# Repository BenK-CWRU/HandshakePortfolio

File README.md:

This repository contains some of the work I have done using simulation software and EDAs such as LTSpice and KiCad.

The FinalSchem_rev7 folder contains the KiCad project files for the amplitude shift keying and frequency shift keying demodulator circuit.

The ASKFSKDemodulatorFinalSchematic.asc file is the LTSpice file to simulate the amplitude shift keying and frequency shift keying demodulator.

DP2OpAmp.asc is an op amp design I made in LTSpice.

LDO is a low dropout linear regulator design I made in LTSpice.

OscillatorFunctionGen.asc is a function generator design I made in LTSpice.

PWMtoOptoDevice.asc is a PWM generator based on an external signal that is coupled to an optoelectronic device to output the same PWM signal. I designed this in LTSpice.

kHzClockGen.asc is an astable oscillator circuit that was made to generate a 1 kHz clock signal, which I designed in LTSpice.

I also have more experience with Autodesk Fusion, but most of the work is closely related to lab work that has yet to be patented.
Without disclosing the whole work, I have designed a circuit that contains a microcontroller which periodically polls an on-board pressure sensor.
It contained wireless power harvesting circuitry, so it could be powered with an inductive link to a source coil.
It was a two-layer board with tight trace routing. I researched the tolerances with our PCB vendor before layout to ensure I could design the smallest board possible.

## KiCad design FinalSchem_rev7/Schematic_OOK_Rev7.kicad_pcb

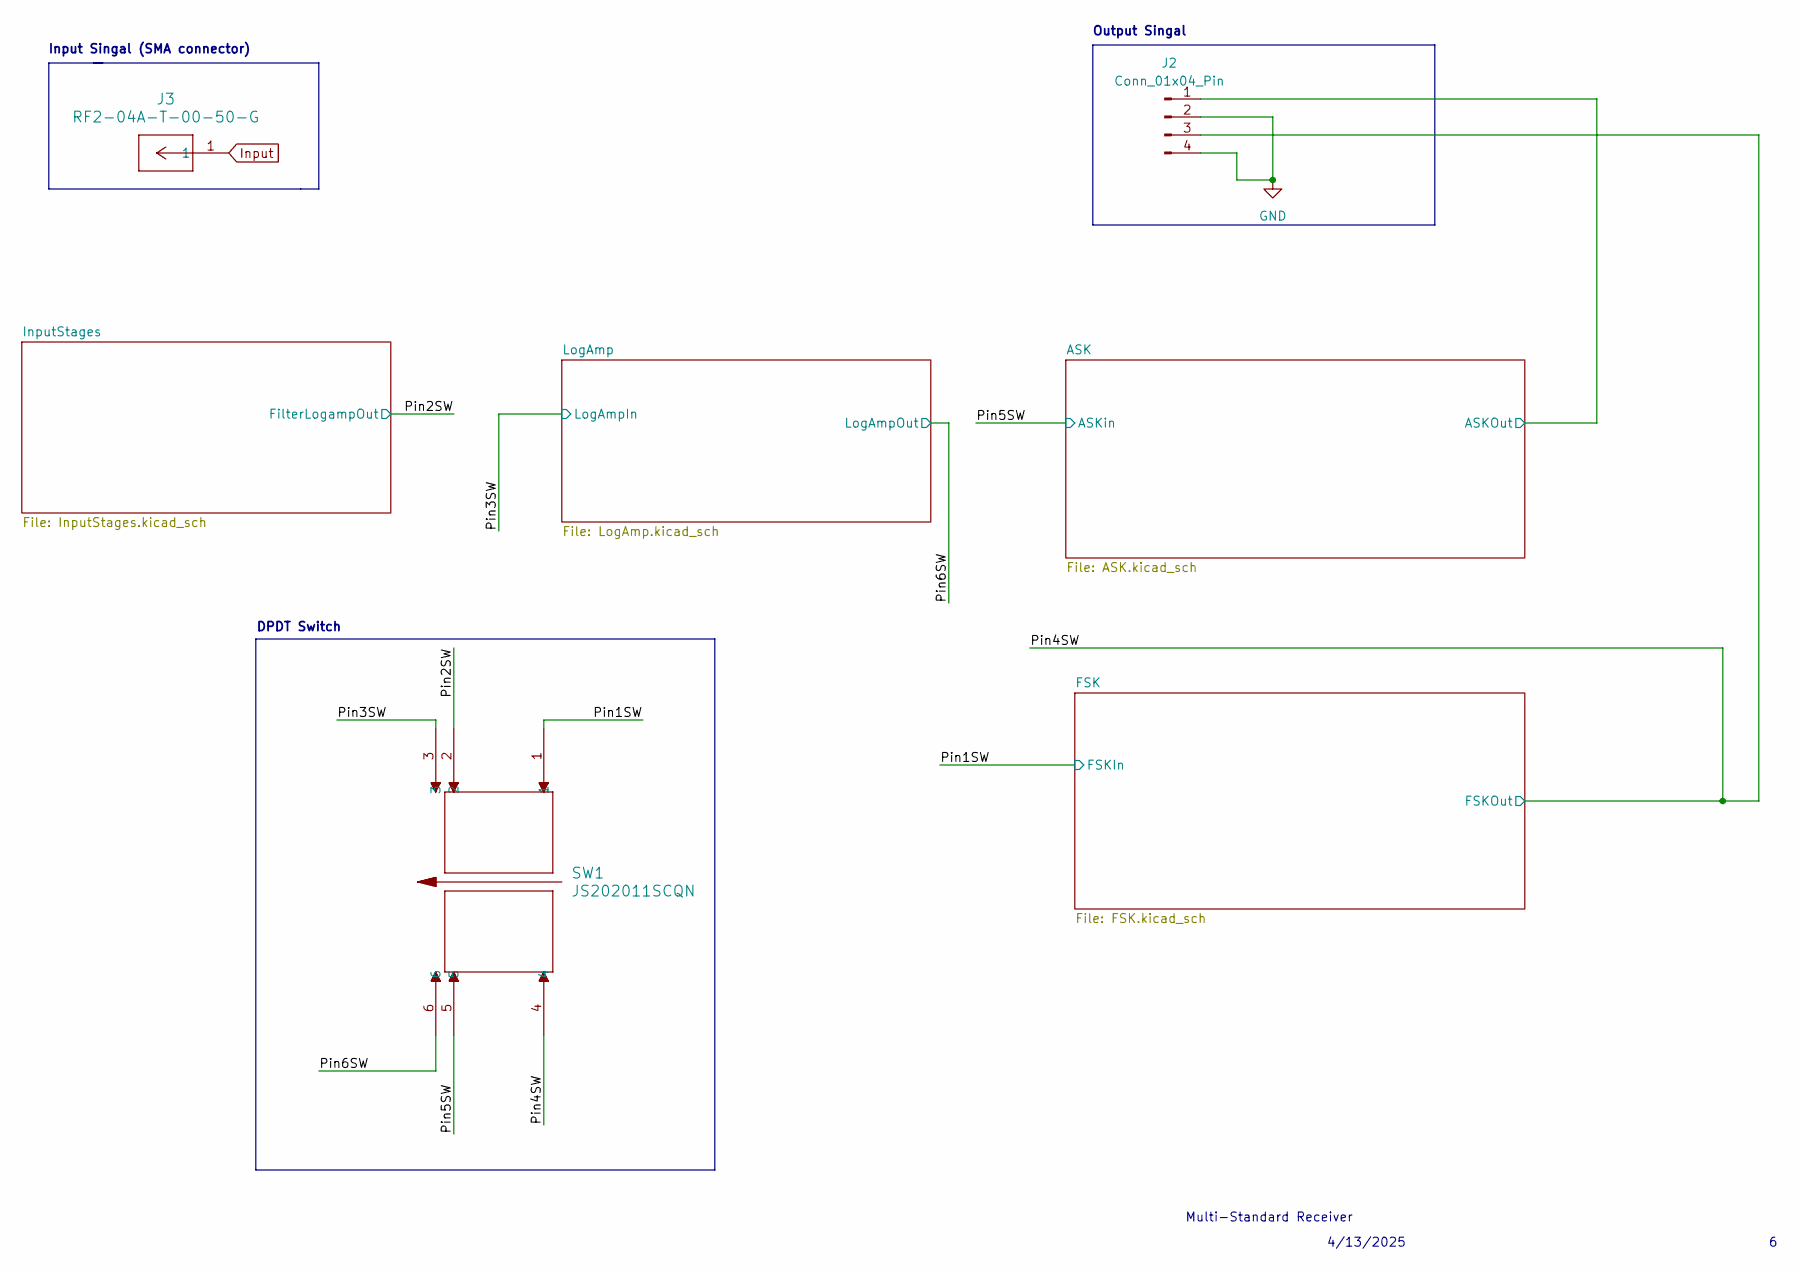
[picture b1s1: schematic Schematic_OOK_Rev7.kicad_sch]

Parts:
J2: Conn_01x04_Pin; PinHeader_1x04_P2.54mm_Vertical
J3: RF2-04A-T-00-50-G; CONN_RF2-04A-T-00-50-G_ADM
SW1: JS202011SCQN

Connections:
/ASK/ASKOut: J2.1; also elsewhere on the board
/Pin1SW: SW1.1; also elsewhere on the board
/Pin2SW: SW1.2; also elsewhere on the board
/Pin3SW: SW1.3; also elsewhere on the board
/Pin4SW: J2.3, SW1.4; also elsewhere on the board
/Pin5SW: SW1.5; also elsewhere on the board
/Pin6SW: SW1.6; also elsewhere on the board
GND: J2.2, J2.4; also elsewhere on the board
Input: J3.1; also elsewhere on the board

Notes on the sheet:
Output Singal
Input Singal (SMA connector)
4/13/2025
Multi-Standard Receiver
DPDT Switch

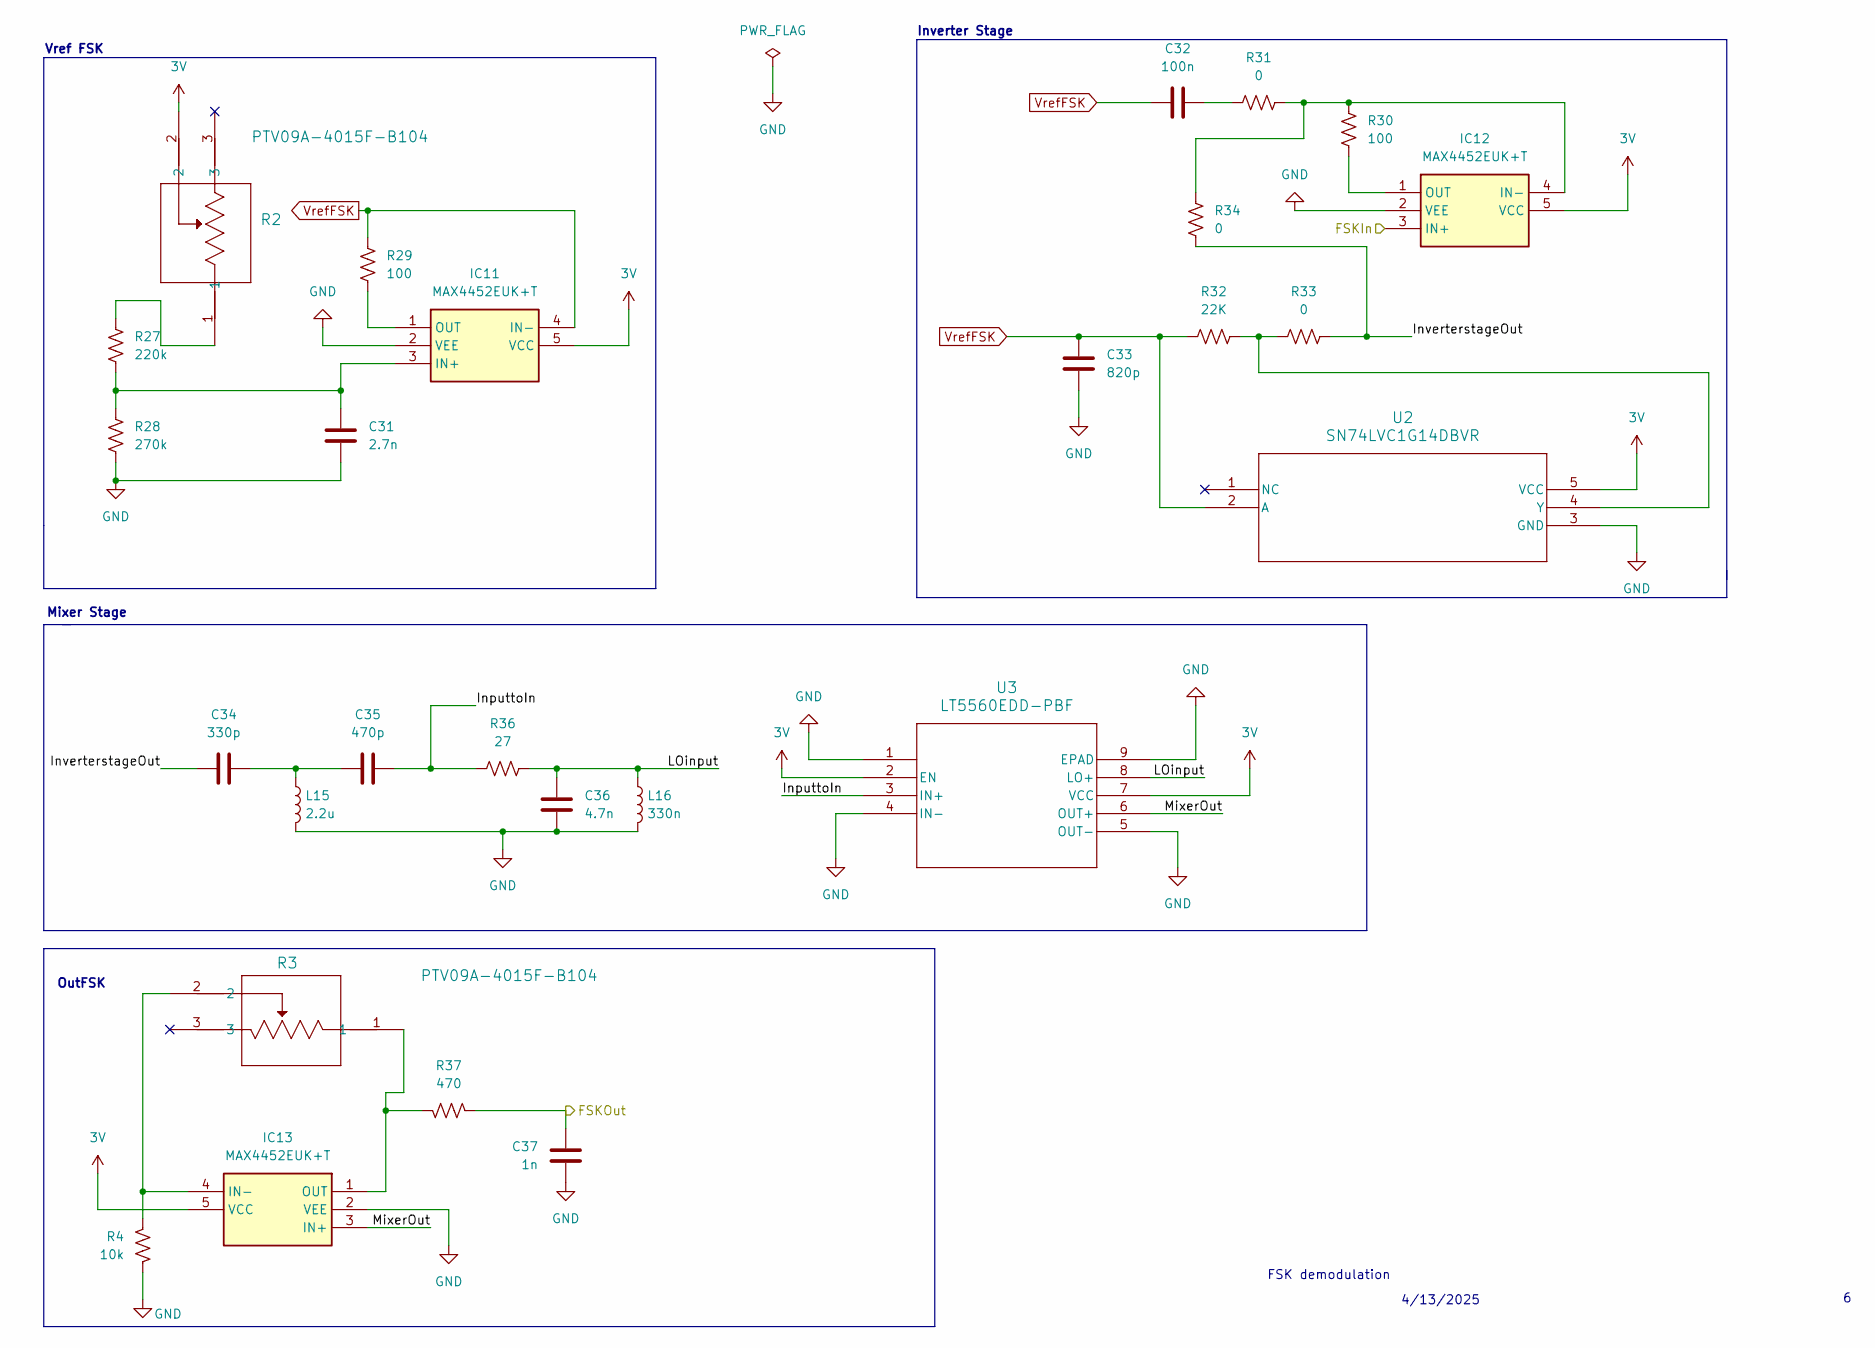
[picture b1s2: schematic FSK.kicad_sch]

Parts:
C31: 2.7n; C_0603_1608Metric
C32: 100n; C_0603_1608Metric
C33: 820p; C_0603_1608Metric
C34: 330p; C_0603_1608Metric
C35: 470p; C_0603_1608Metric
C36: 4.7n; C_0603_1608Metric
C37: 1n; C_0603_1608Metric
IC11, IC12, IC13: MAX4452EUK+T; SOT95P280X145-5N; Mouser Part Number 700-MAX4452EUKT
L15: 2.2u; L_0603_1608Metric
L16: 330n; L_0603_1608Metric
R2, R3: PTV09A-4015F-B104; PTV09A-4015F-B104_BRN
R4: 10k; R_0603_1608Metric
R27: 220k; R_0603_1608Metric
R28: 270k; R_0603_1608Metric
R29, R30: 100; R_0603_1608Metric
R31, R33, R34: 0; R_0603_1608Metric
R32: 22K; R_0603_1608Metric
R36: 27; R_0603_1608Metric
R37: 470; R_0603_1608Metric
U2: SN74LVC1G14DBVR
U3: LT5560EDD-PBF; LT556EDD-PBF

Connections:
3V: IC11.5 (VCC), IC12.5 (VCC), IC13.5 (VCC), R2.2, U2.5 (VCC), U3.2 (EN), U3.7 (VCC); also elsewhere on the board
/FSK/InputtoIn: C35.2, R36.1, U3.3 (IN+)
/FSK/InverterstageOut: C34.1, R33.2, R34.1
/FSK/LOinput: C36.2, L16.1, R36.2, U3.8 (LO+)
/FSK/MixerOut: IC13.3 (IN+), U3.6 (OUT+)
/Pin1SW: IC12.3 (IN+); also elsewhere on the board
/Pin4SW: C37.2, R37.2; also elsewhere on the board
GND: C31.1, C33.1, C36.1, C37.1, IC11.2 (VEE), IC12.2 (VEE), IC13.2 (VEE), L15.2, L16.2, R4.2, R28.2, U2.3 (GND), U3.1, U3.4 (IN-), U3.5 (OUT-), U3.9 (EPAD); also elsewhere on the board
unnamed: C32.1, R31.1
unnamed: C34.2, C35.1, L15.1
unnamed: C31.2, IC11.3 (IN+), R27.2, R28.1
unnamed: IC11.1 (OUT), R29.2
unnamed: IC12.4 (IN-), R30.1, R31.2, R34.2
unnamed: IC12.1 (OUT), R30.2
unnamed: IC13.4 (IN-), R3.2, R4.1
unnamed: IC13.1 (OUT), R3.1, R37.1
unnamed: R2.1, R27.1
unnamed: R32.1, R33.1, U2.4 (Y)
VrefFSK: C32.2, C33.2, IC11.4 (IN-), R29.1, R32.2, U2.2 (A)

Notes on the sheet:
Mixer Stage
Vref FSK
FSK demodulation
4/13/2025
Inverter Stage
OutFSK

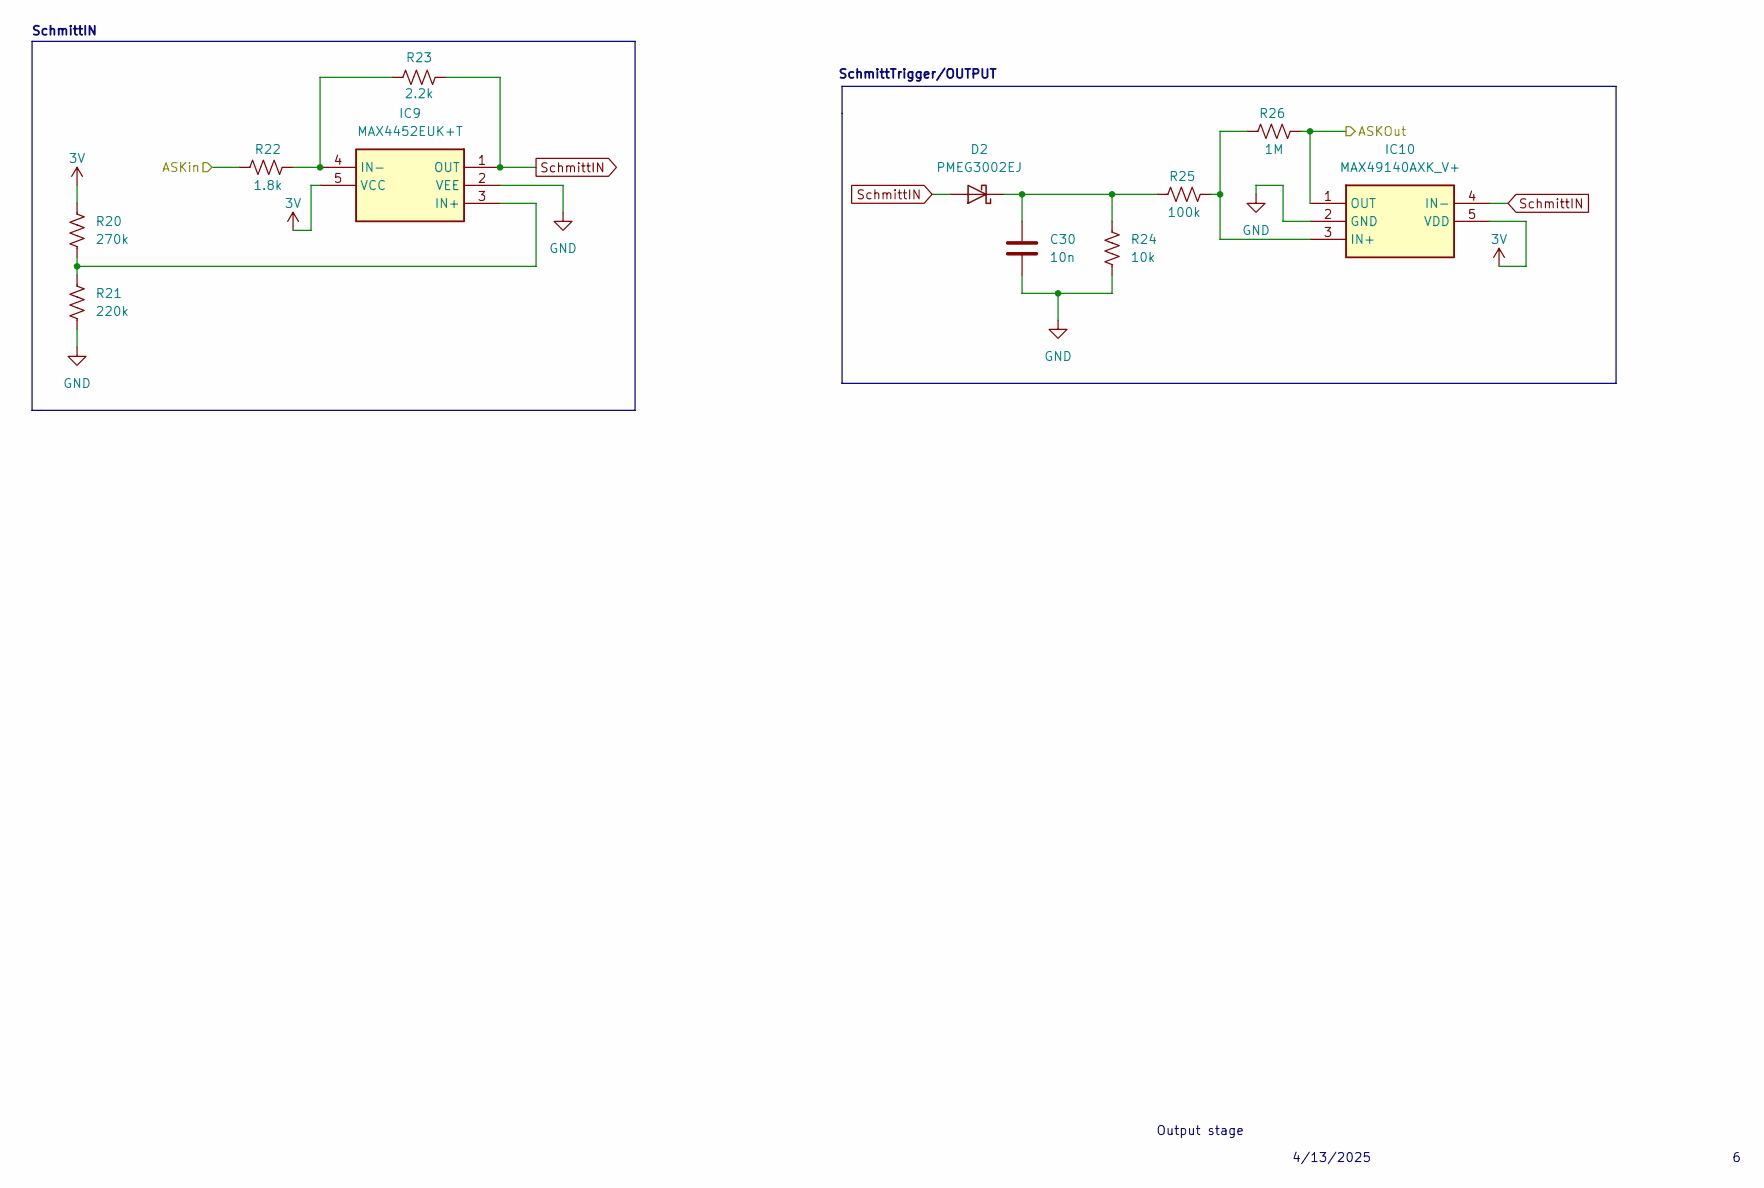
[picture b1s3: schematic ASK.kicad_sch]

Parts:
C30: 10n; C_0603_1608Metric
D2: PMEG3002EJ; D_SOD-323F
IC9: MAX4452EUK+T; SOT95P280X145-5N; Mouser Part Number 700-MAX4452EUKT
IC10: MAX49140AXK_V+; SOT65P210X110-5N; Mouser Part Number 700-MAX49140AXK/V+
R20: 270k; R_0603_1608Metric
R21: 220k; R_0603_1608Metric
R22: 1.8k; R_0603_1608Metric
R23: 2.2k; R_0603_1608Metric
R24: 10k; R_0603_1608Metric
R25: 100k; R_0603_1608Metric
R26: 1M; R_0603_1608Metric

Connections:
3V: IC9.5 (VCC), IC10.5 (VDD), R20.1; also elsewhere on the board
/ASK/ASKOut: IC10.1 (OUT), R26.2; also elsewhere on the board
/Pin5SW: R22.2; also elsewhere on the board
GND: C30.1, IC9.2 (VEE), IC10.2 (GND), R21.2, R24.2; also elsewhere on the board
unnamed: C30.2, D2.1 (K), R24.1, R25.1
unnamed: IC9.3 (IN+), R20.2, R21.1
unnamed: IC9.4 (IN-), R22.1, R23.1
unnamed: IC10.3 (IN+), R25.2, R26.1
SchmittIN: D2.2 (A), IC9.1 (OUT), IC10.4 (IN-), R23.2

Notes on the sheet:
SchmittTrigger/OUTPUT
4/13/2025
SchmittIN
Output stage

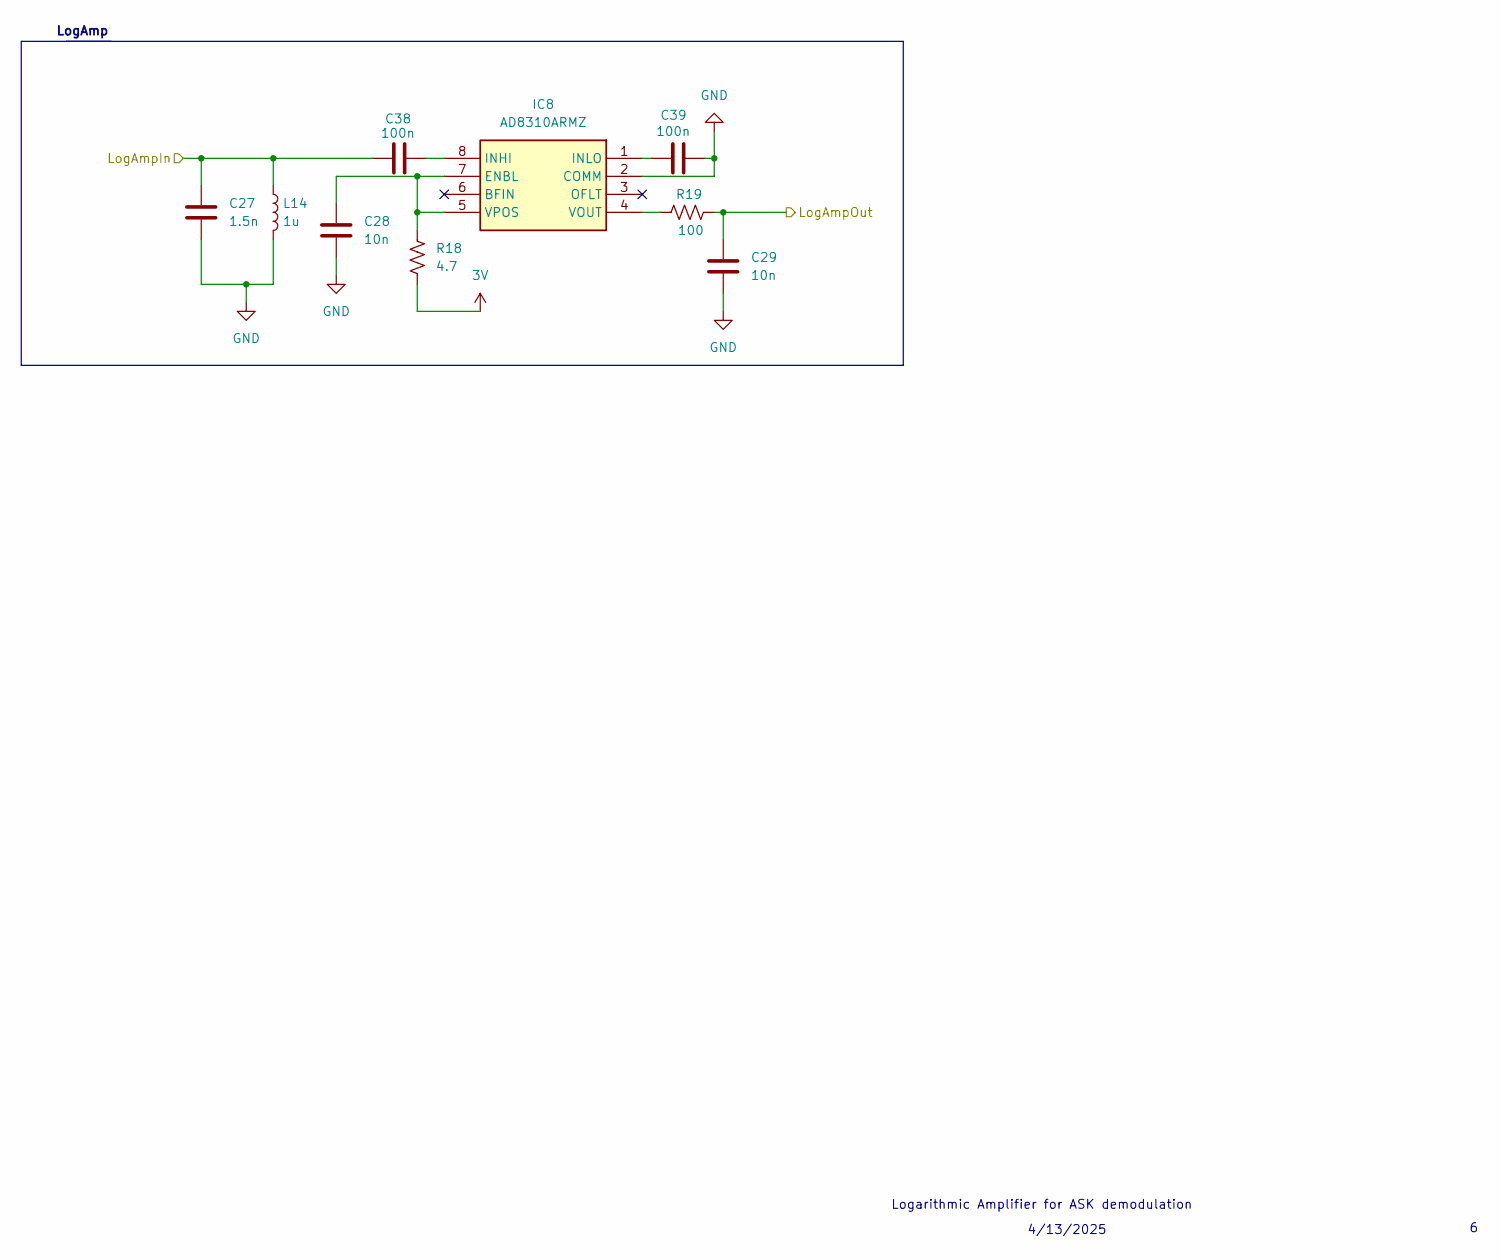
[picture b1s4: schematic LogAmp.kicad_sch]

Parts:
C27: 1.5n; C_0603_1608Metric
C28, C29: 10n; C_0603_1608Metric
C38, C39: 100n; C_0603_1608Metric
IC8: AD8310ARMZ; SOP65P490X110-8N; Mouser Part Number 584-AD8310ARMZ
L14: 1u; L_0603_1608Metric
R18: 4.7; R_0603_1608Metric
R19: 100; R_0603_1608Metric

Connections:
3V: R18.2; also elsewhere on the board
/Pin3SW: C27.2, C38.2, L14.1; also elsewhere on the board
/Pin6SW: C29.2, R19.1; also elsewhere on the board
GND: C27.1, C28.1, C29.1, C39.1, IC8.2 (COMM), L14.2; also elsewhere on the board
unnamed: C28.2, IC8.5 (VPOS), IC8.7 (ENBL), R18.1
unnamed: C38.1, IC8.8 (INHI)
unnamed: C39.2, IC8.1 (INLO)
unnamed: IC8.4 (VOUT), R19.2

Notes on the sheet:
4/13/2025
LogAmp
Logarithmic Amplifier for ASK demodulation

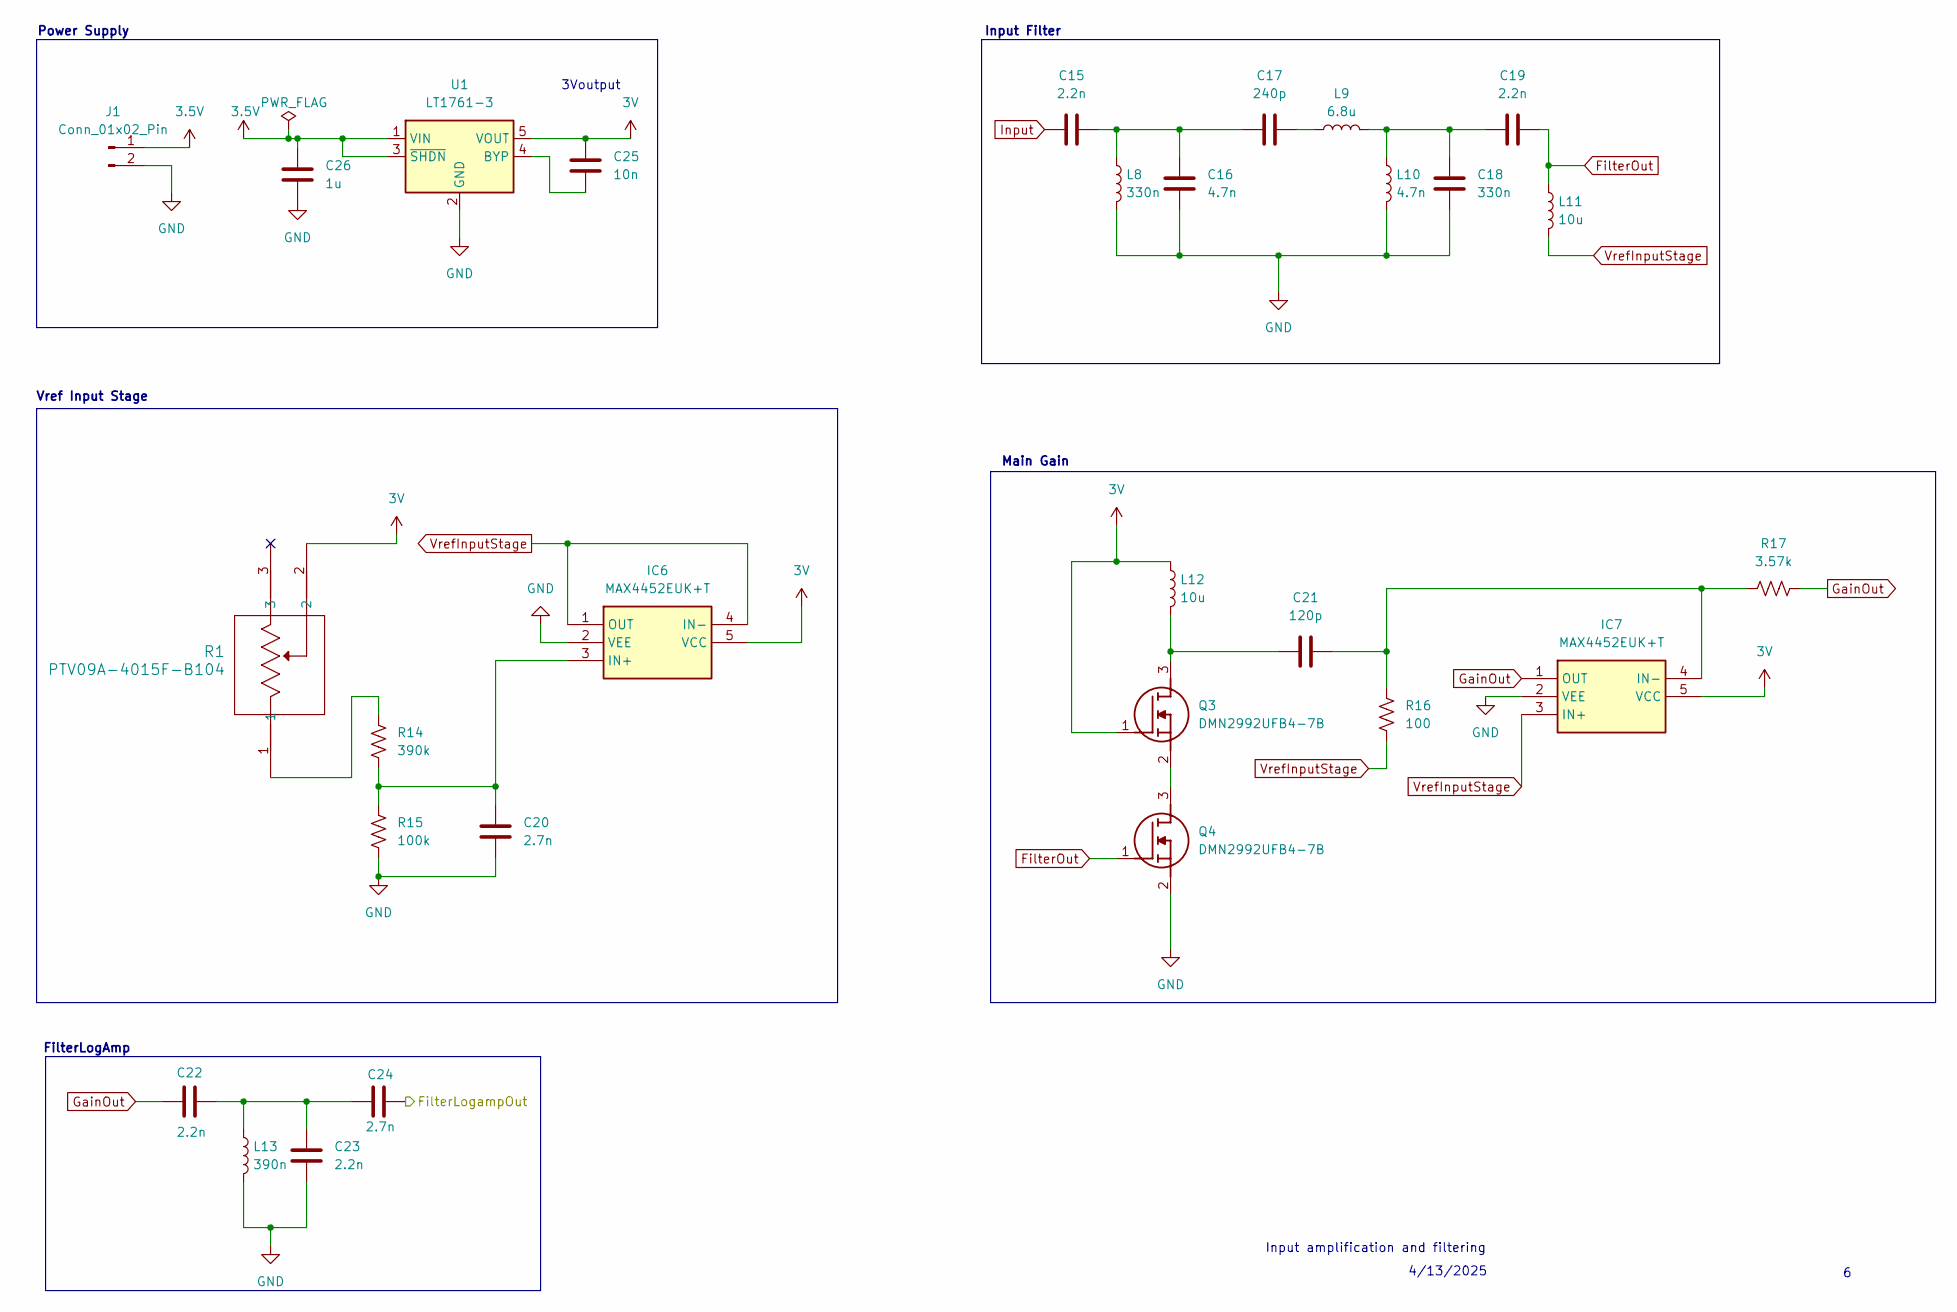
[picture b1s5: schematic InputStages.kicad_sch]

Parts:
C15, C19, C22, C23: 2.2n; C_0603_1608Metric
C16: 4.7n; C_0603_1608Metric
C17: 240p; C_0603_1608Metric
C18: 330n; C_0603_1608Metric
C20, C24: 2.7n; C_0603_1608Metric
C21: 120p; C_0603_1608Metric
C25: 10n; C_0603_1608Metric
C26: 1u; C_0603_1608Metric
IC6, IC7: MAX4452EUK+T; SOT95P280X145-5N; Mouser Part Number 700-MAX4452EUKT
J1: Conn_01x02_Pin; PinHeader_1x02_P2.54mm_Vertical
L8: 330n; L_0603_1608Metric
L9: 6.8u; L_0603_1608Metric
L10: 4.7n; L_0603_1608Metric
L11, L12: 10u; L_0603_1608Metric
L13: 390n; L_0603_1608Metric
Q3, Q4: DMN2992UFB4-7B; DMN2992UFB47B; Manufacturer_Part_Number DMN2992UFB4-7B
R1: PTV09A-4015F-B104; PTV09A-4015F-B104_BRN
R14: 390k; R_0603_1608Metric
R15: 100k; R_0603_1608Metric
R16: 100; R_0603_1608Metric
R17: 3.57k; R_0603_1608Metric
U1: LT1761-3; TSOT-23-5

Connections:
3.5V: C26.2, J1.1, U1.1 (VIN), U1.3 (~SHDN)
3V: C25.2, IC6.5 (VCC), IC7.5 (VCC), L12.1, Q3.1 (G), R1.2, U1.5 (VOUT); also elsewhere on the board
/Pin2SW: C24.1; also elsewhere on the board
FilterOut: C19.1, L11.1, Q4.1 (G)
GND: C16.1, C18.1, C20.1, C23.1, C26.1, IC6.2 (VEE), IC7.2 (VEE), J1.2, L8.2, L10.2, L13.2, Q4.2 (S), R15.2, U1.2 (GND); also elsewhere on the board
GainOut: C22.1, IC7.1 (OUT), R17.2
Input: C15.1; also elsewhere on the board
unnamed: C15.2, C16.2, C17.1, L8.1
unnamed: C17.2, L9.1
unnamed: C18.2, C19.2, L9.2, L10.1
unnamed: C22.2, C23.2, C24.2, L13.1
unnamed: C20.2, IC6.3 (IN+), R14.2, R15.1
unnamed: C21.1, IC7.4 (IN-), R16.1, R17.1
unnamed: C21.2, L12.2, Q3.3 (D)
unnamed: Q3.2 (S), Q4.3 (D)
unnamed: R1.1, R14.1
unnamed: C25.1, U1.4 (BYP)
VrefInputStage: IC6.1 (OUT), IC6.4 (IN-), IC7.3 (IN+), L11.2, R16.2

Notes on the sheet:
FilterLogAmp
Main Gain
4/13/2025
Input amplification and filtering
3Voutput
Vref Input Stage
Power Supply
Input Filter

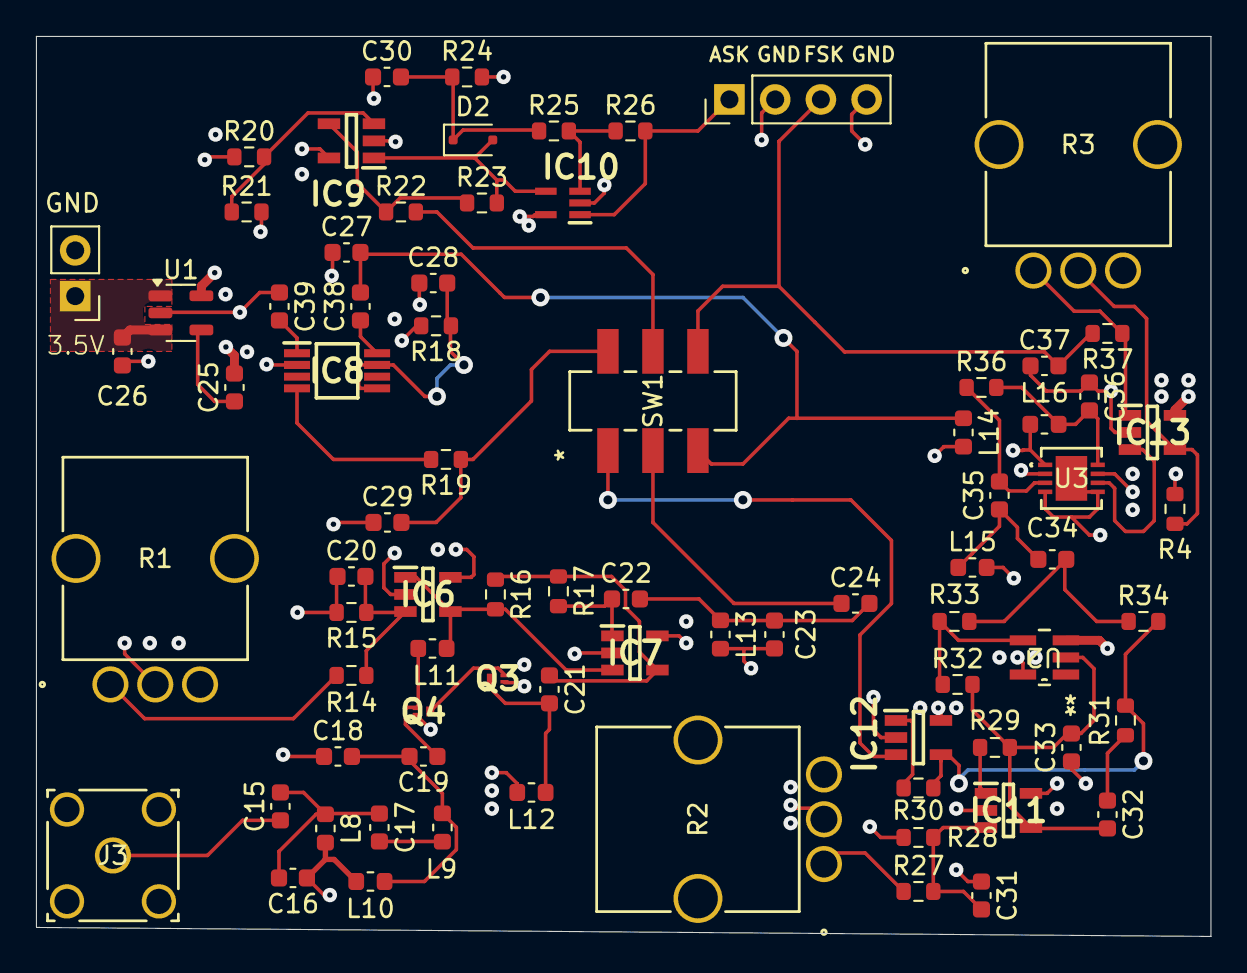
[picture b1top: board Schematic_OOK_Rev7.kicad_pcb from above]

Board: 4 copper layers, 65.2 x 50.0 mm, 79 parts (0 on the bottom side), 48 nets.

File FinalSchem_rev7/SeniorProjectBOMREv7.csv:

Reference,Qty,Value,DNP,Footprint,Datasheet
"C15,C19,C22,C23",4,2.2n,,Capacitor_SMD:C_0603_1608Metric,~
"C16,C36",2,4.7n,,Capacitor_SMD:C_0603_1608Metric,~
C17,1,240p,,Capacitor_SMD:C_0603_1608Metric,~
C18,1,330n,,Capacitor_SMD:C_0603_1608Metric,~
"C20,C24,C31",3,2.7n,,Capacitor_SMD:C_0603_1608Metric,~
C21,1,120p,,Capacitor_SMD:C_0603_1608Metric,~
"C25,C28,C29,C30",4,10n,,Capacitor_SMD:C_0603_1608Metric,~
C26,1,1u,,Capacitor_SMD:C_0603_1608Metric,~
C27,1,1.5n,,Capacitor_SMD:C_0603_1608Metric,~
"C32,C38,C39",3,100n,,Capacitor_SMD:C_0603_1608Metric,~
C33,1,820p,,Capacitor_SMD:C_0603_1608Metric,~
C34,1,330p,,Capacitor_SMD:C_0603_1608Metric,~
C35,1,470p,,Capacitor_SMD:C_0603_1608Metric,~
C37,1,1n,,Capacitor_SMD:C_0603_1608Metric,~
D2,1,PMEG3002EJ,,Diode_SMD:D_SOD-323F,https://assets.nexperia.com/documents/data-sheet/PMEG3002EJ.pdf
"IC6,IC7,IC9,IC11,IC12,IC13",6,MAX4452EUK+T,,MAX4452EUK+T:SOT95P280X145-5N,https://pdfserv.maximintegrated.com/en/ds/MAX4352-MAX4454.pdf
IC8,1,AD8310ARMZ,,AD8310ARMZ:SOP65P490X110-8N,http://www.analog.com/static/imported-files/data_sheets/AD8310.pdf
IC10,1,MAX49140AXK_V+,,MAX49140AXK_V+:SOT65P210X110-5N,https://pdfserv.maximintegrated.com/en/ds/MAX49140.pdf
J1,1,Conn_01x02_Pin,,Connector_PinHeader_2.54mm:PinHeader_1x02_P2.54mm_Vertical,~
J2,1,Conn_01x04_Pin,,Connector_PinHeader_2.54mm:PinHeader_1x04_P2.54mm_Vertical,~
J3,1,RF2-04A-T-00-50-G,,RF2_04A_T_00_50_G:CONN_RF2-04A-T-00-50-G_ADM,RF2-04A-T-00-50-G
"L8,L16",2,330n,,Inductor_SMD:L_0603_1608Metric,~
L9,1,6.8u,,Inductor_SMD:L_0603_1608Metric,~
L10,1,4.7n,,Inductor_SMD:L_0603_1608Metric,~
"L11,L12",2,10u,,Inductor_SMD:L_0603_1608Metric,~
L13,1,390n,,Inductor_SMD:L_0603_1608Metric,~
L14,1,1u,,Inductor_SMD:L_0603_1608Metric,~
L15,1,2.2u,,Inductor_SMD:L_0603_1608Metric,~
"Q3,Q4",2,DMN2992UFB4-7B,,DMN2992UFB4-7B:DMN2992UFB47B,https://www.diodes.com/assets/Datasheets/DMN2992UFB4.pdf
"R1,R2,R3",3,PTV09A-4015F-B104,,PTV09A_4015F_B104:PTV09A-4015F-B104_BRN,PTV09A-4015F-B104
"R4,R24",2,10k,,Resistor_SMD:R_0603_1608Metric,~
R14,1,390k,,Resistor_SMD:R_0603_1608Metric,~
"R15,R25",2,100k,,Resistor_SMD:R_0603_1608Metric,~
"R16,R19,R29,R30",4,100,,Resistor_SMD:R_0603_1608Metric,~
R17,1,3.57k,,Resistor_SMD:R_0603_1608Metric,~
R18,1,4.7,,Resistor_SMD:R_0603_1608Metric,~
"R20,R28",2,270k,,Resistor_SMD:R_0603_1608Metric,~
"R21,R27",2,220k,,Resistor_SMD:R_0603_1608Metric,~
R22,1,1.8k,,Resistor_SMD:R_0603_1608Metric,~
R23,1,2.2k,,Resistor_SMD:R_0603_1608Metric,~
R26,1,1M,,Resistor_SMD:R_0603_1608Metric,~
"R31,R33,R34",3,0,Yes,Resistor_SMD:R_0603_1608Metric,~
R32,1,22K,,Resistor_SMD:R_0603_1608Metric,~
R36,1,27,,Resistor_SMD:R_0603_1608Metric,~
R37,1,470,,Resistor_SMD:R_0603_1608Metric,~
SW1,1,JS202011SCQN,,JS202011SCQN:JS202011SCQN,JS202011SCQN
U1,1,LT1761-3,,Package_TO_SOT_SMD:TSOT-23-5,https://www.analog.com/media/en/technical-documentation/data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
U2,1,SN74LVC1G14DBVR,,ul_SN74LVC1G14DBVR:SN74LVC1G14DBVR,SN74LVC1G14DBVR
U3,1,LT5560EDD-PBF,,LT5560EDD_PBF:LT556EDD-PBF,LT5560EDD-PBF

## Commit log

2026-04-26 Added files to showcase
2026-04-26 Added senior project files
